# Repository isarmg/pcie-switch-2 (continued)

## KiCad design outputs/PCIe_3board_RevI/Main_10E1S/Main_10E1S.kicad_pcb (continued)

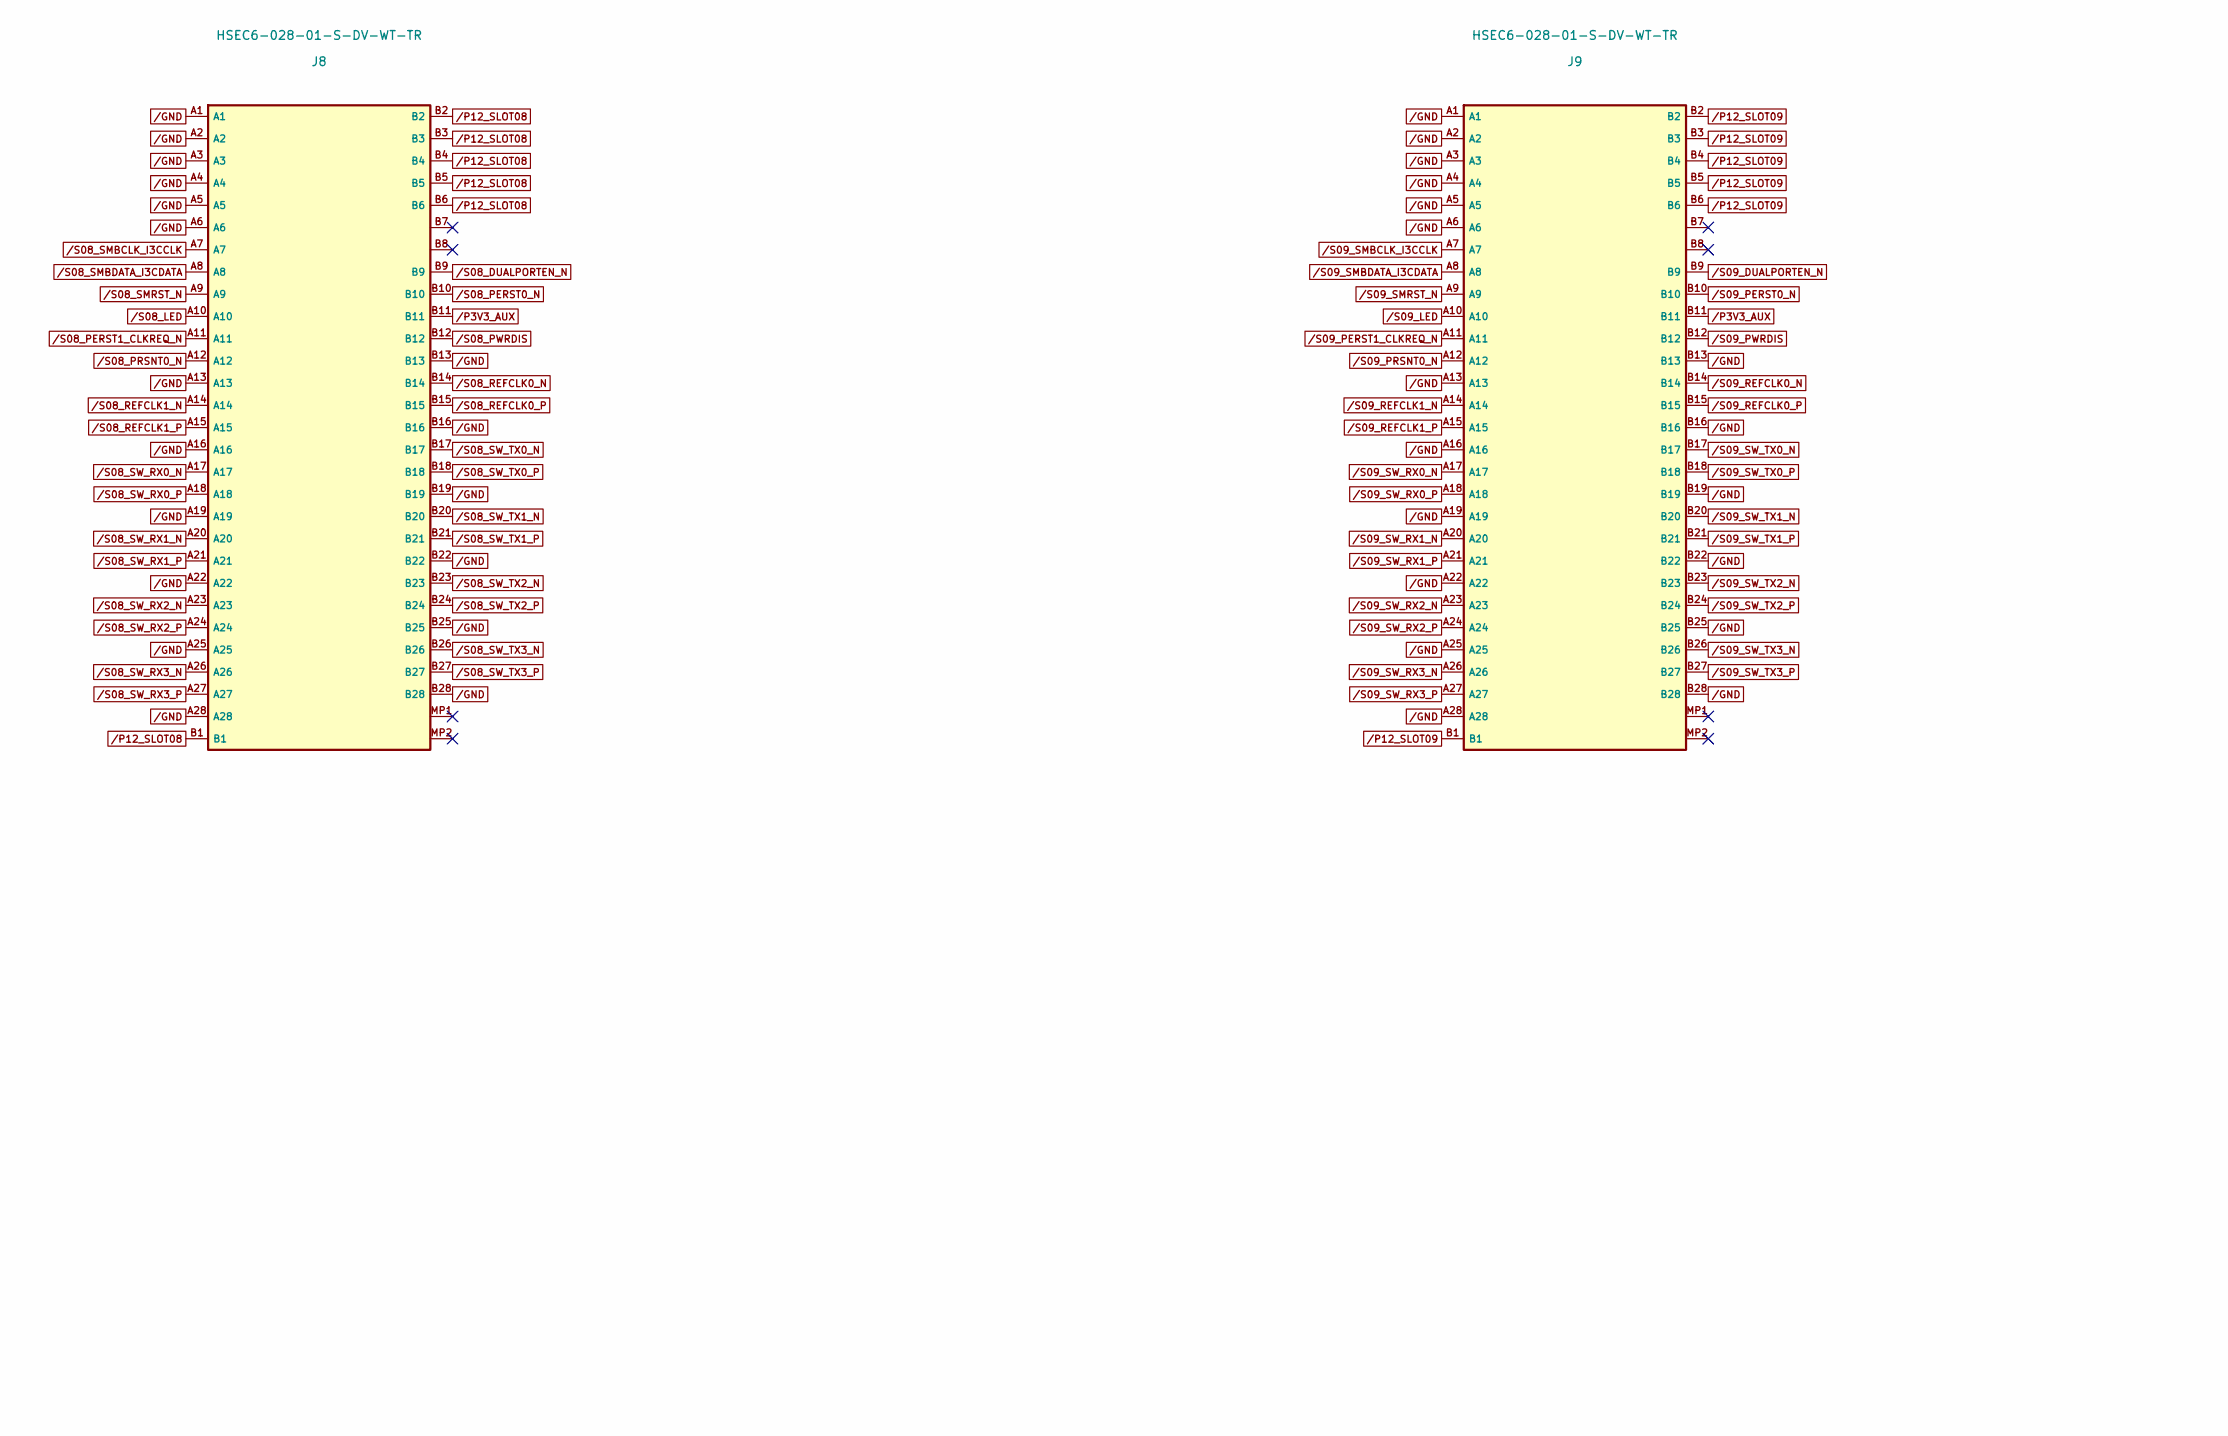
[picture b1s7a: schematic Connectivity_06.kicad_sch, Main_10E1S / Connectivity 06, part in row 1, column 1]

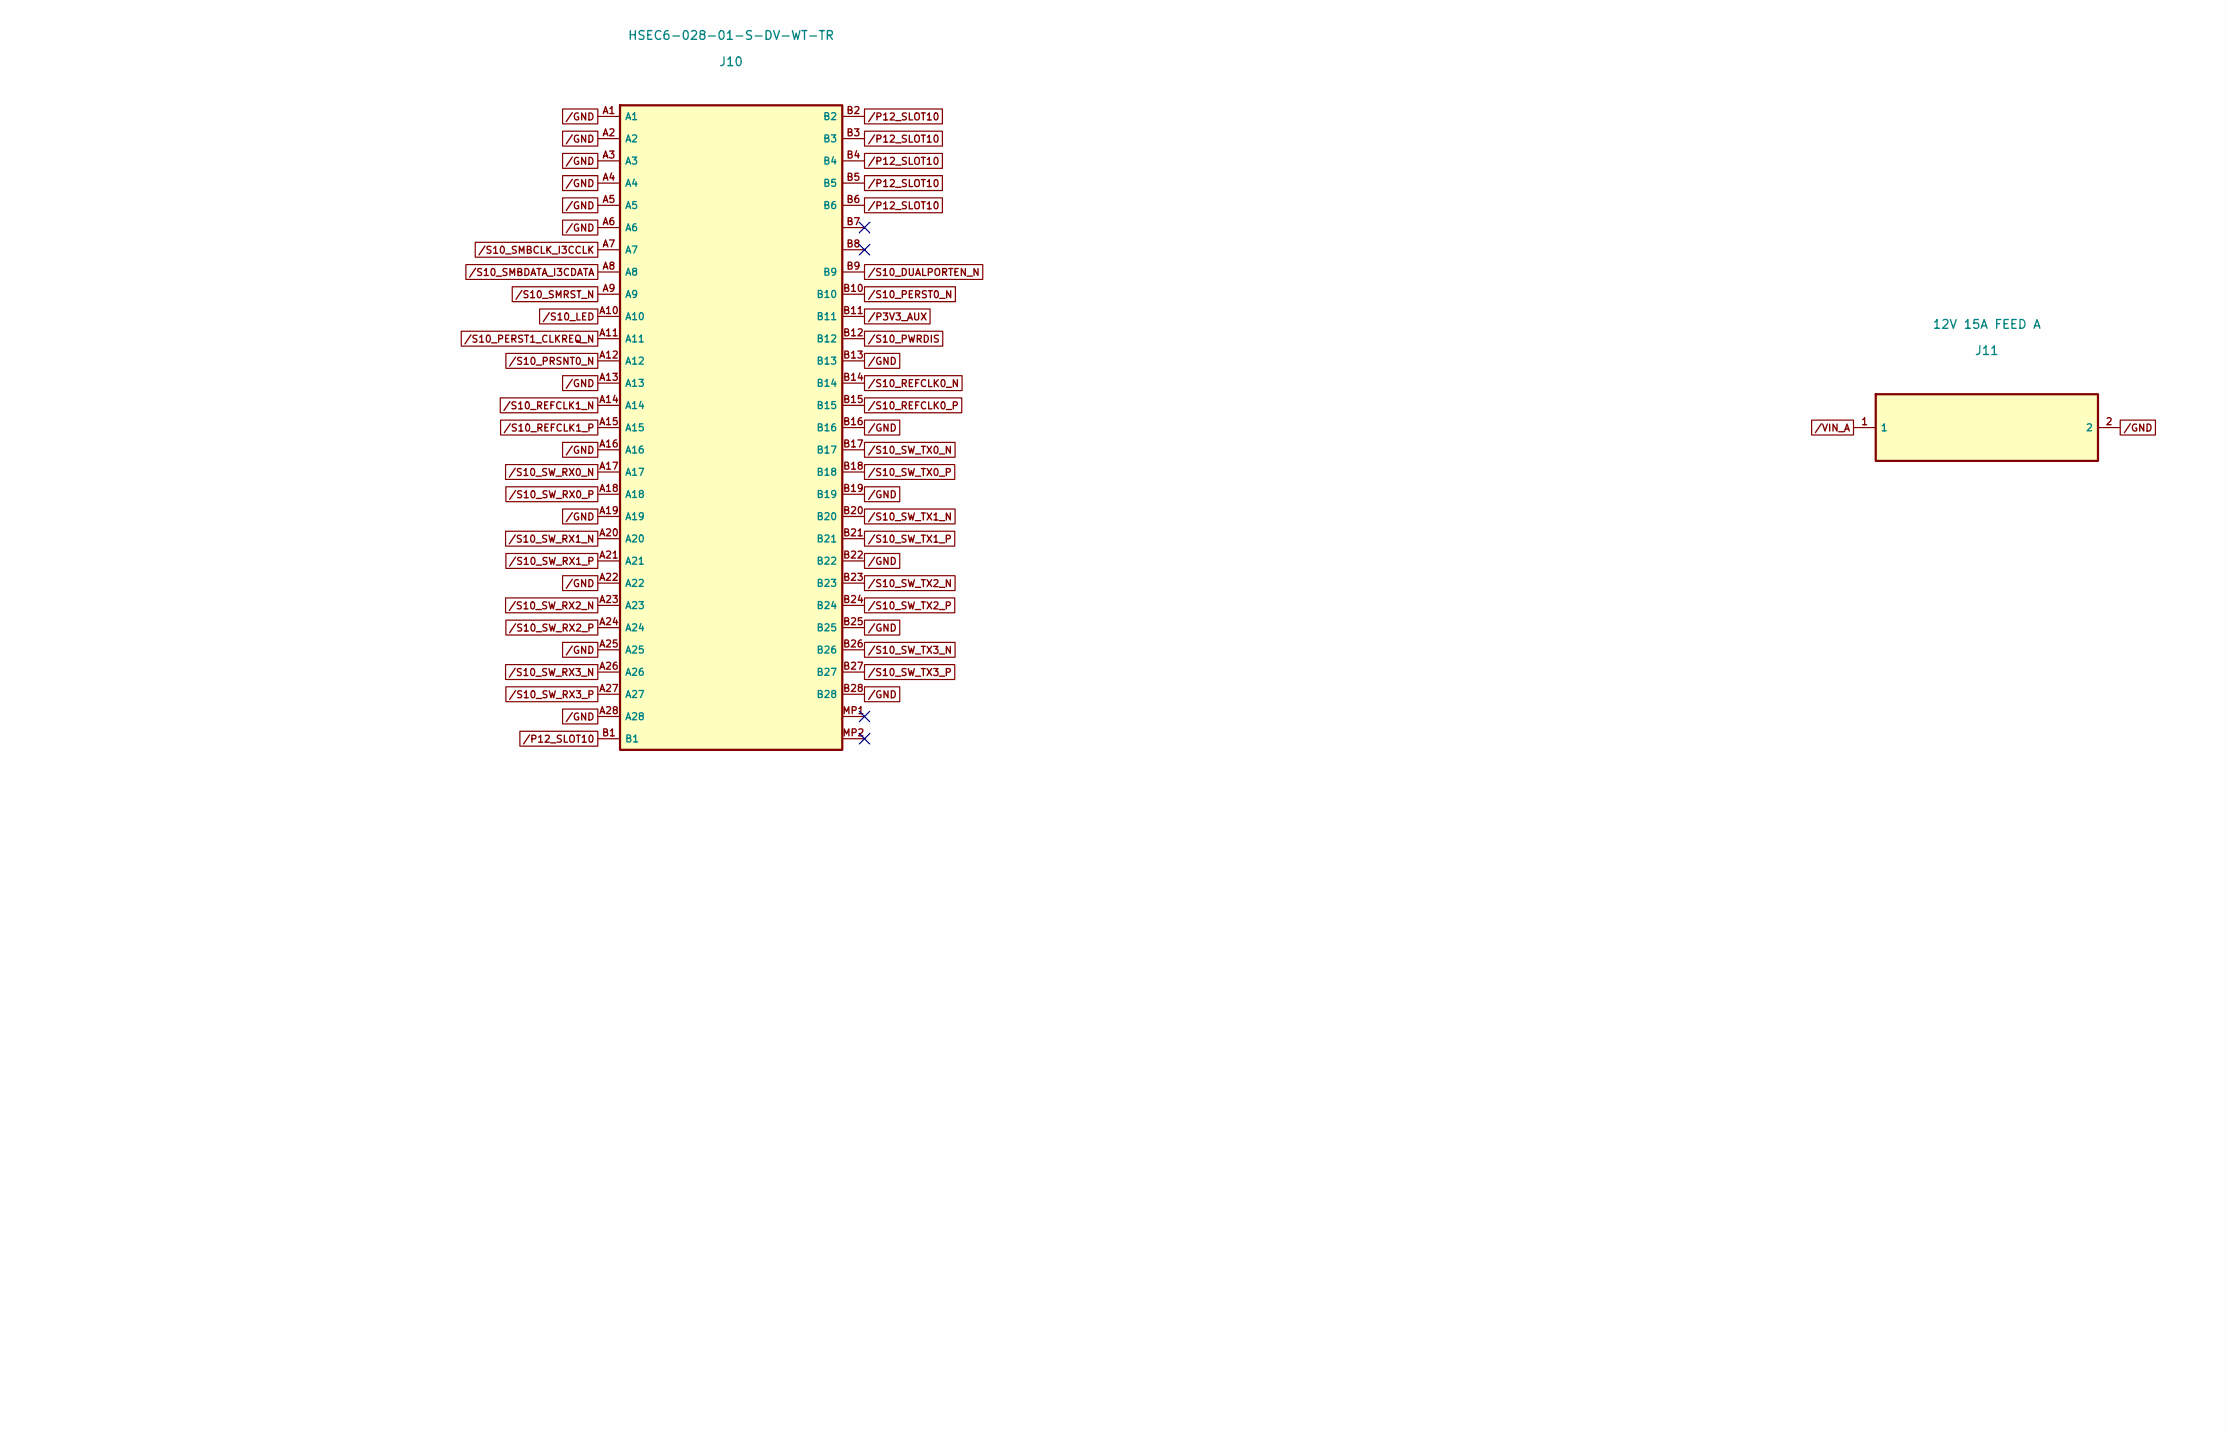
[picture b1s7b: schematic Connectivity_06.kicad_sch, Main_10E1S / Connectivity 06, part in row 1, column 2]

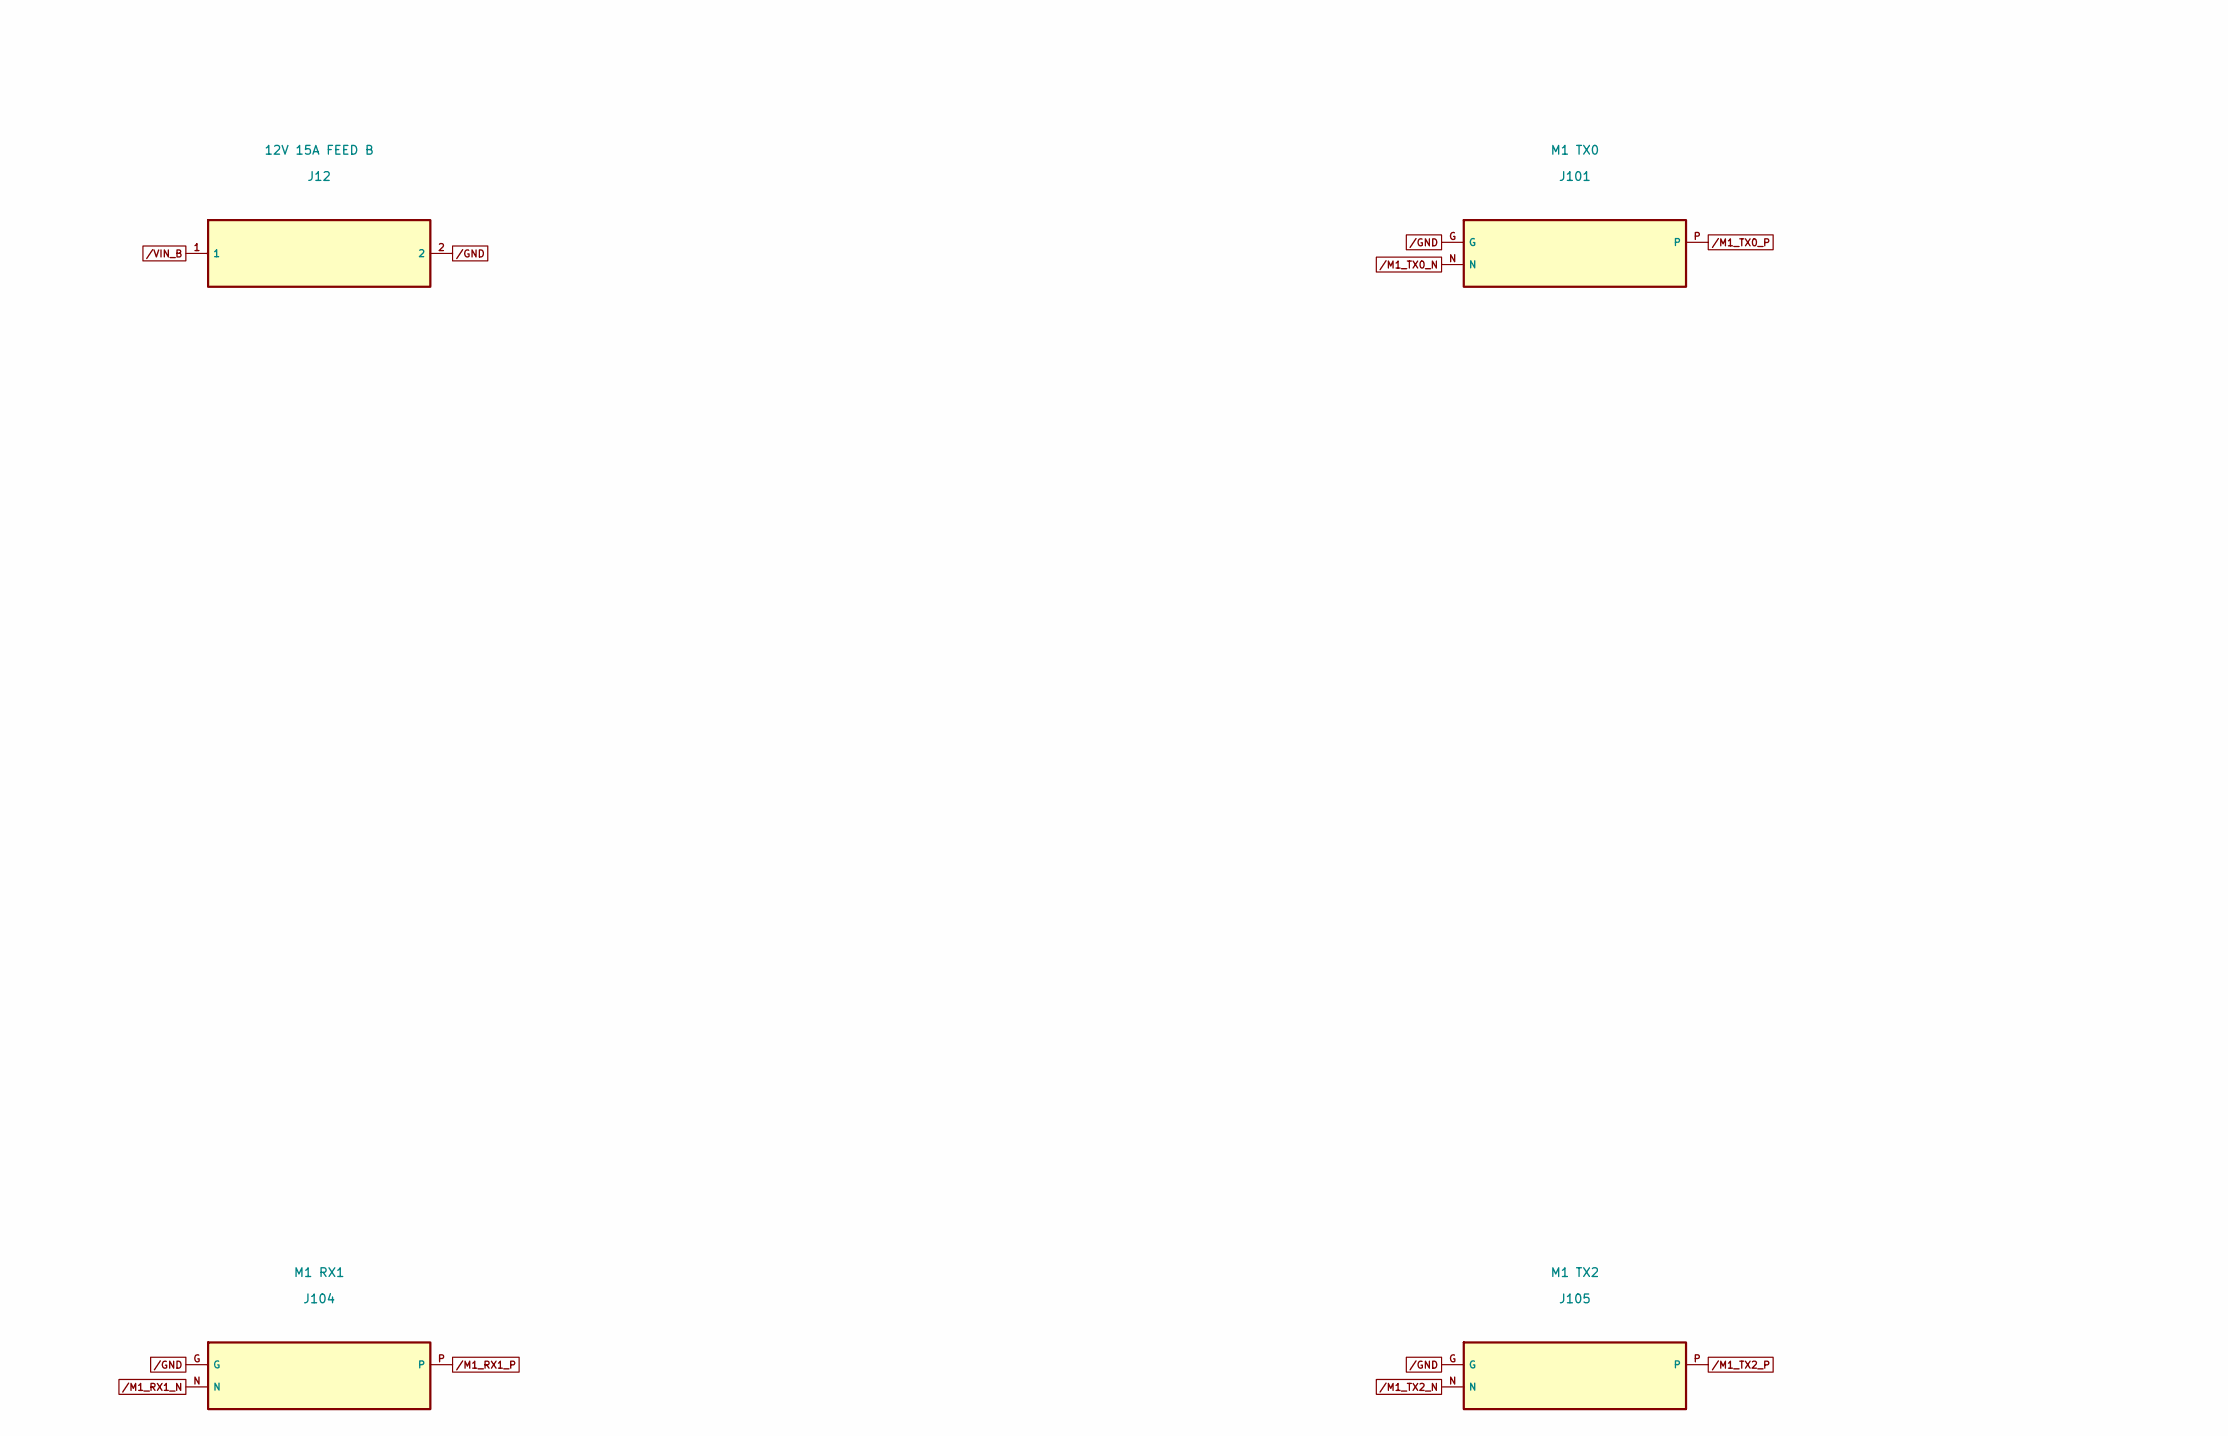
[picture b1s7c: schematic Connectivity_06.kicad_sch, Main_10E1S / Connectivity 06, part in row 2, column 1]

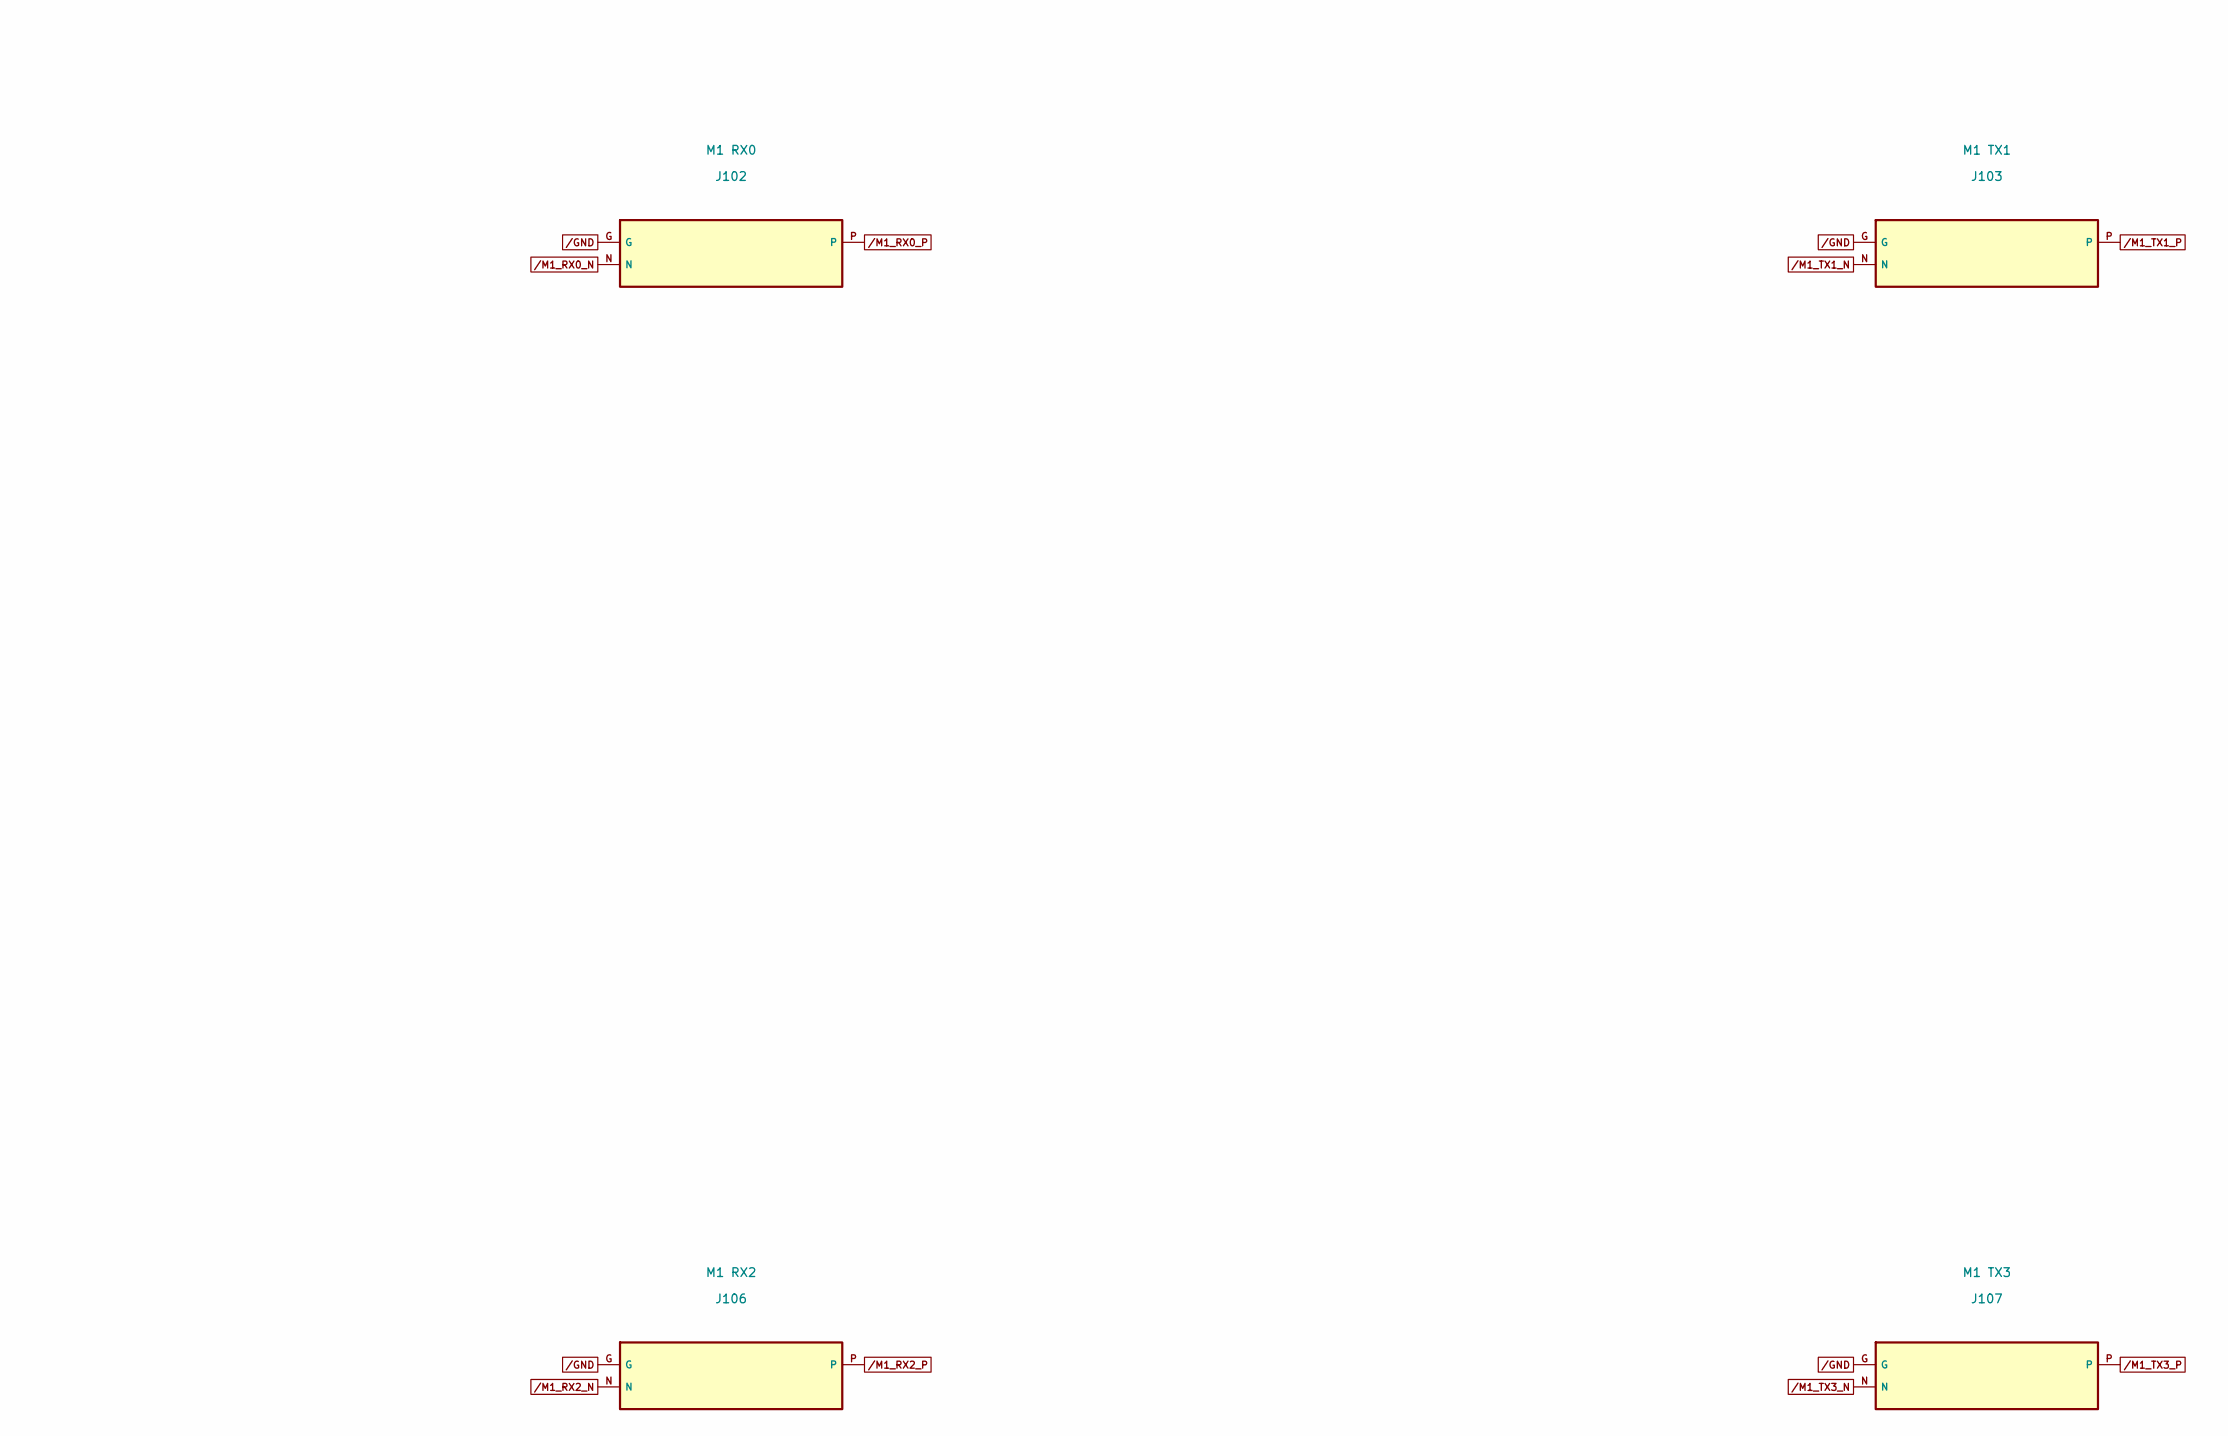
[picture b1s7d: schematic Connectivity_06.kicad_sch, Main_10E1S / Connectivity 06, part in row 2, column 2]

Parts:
J8, J9, J10: HSEC6-028-01-S-DV-WT-TR; Samtec_HSEC6-028-01-S-DV-WT
J11: 12V 15A FEED A; WireSolder_2x_8x5_P12
J12: 12V 15A FEED B; WireSolder_2x_8x5_P12
J101: M1 TX0; Twinax_85R_Solder_DRAFT
J102: M1 RX0; Twinax_85R_Solder_DRAFT
J103: M1 TX1; Twinax_85R_Solder_DRAFT
J104: M1 RX1; Twinax_85R_Solder_DRAFT
J105: M1 TX2; Twinax_85R_Solder_DRAFT
J106: M1 RX2; Twinax_85R_Solder_DRAFT
J107: M1 TX3; Twinax_85R_Solder_DRAFT

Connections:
/GND: J8.A1, J8.A2, J8.A3, J8.A4, J8.A5, J8.A6, J8.A13, J8.A16, J8.A19, J8.A22, J8.A25, J8.A28, J8.B13, J8.B16, J8.B19, J8.B22, J8.B25, J8.B28, J9.A1, J9.A2, J9.A3, J9.A4, J9.A5, J9.A6, J9.A13, J9.A16, J9.A19, J9.A22, J9.A25, J9.A28, J9.B13, J9.B16, J9.B19, J9.B22, J9.B25, J9.B28, J10.A1, J10.A2, J10.A3, J10.A4, J10.A5, J10.A6, J10.A13, J10.A16, J10.A19, J10.A22, J10.A25, J10.A28, J10.B13, J10.B16, J10.B19, J10.B22, J10.B25, J10.B28, J11.2, J12.2, J101.G, J102.G, J103.G, J104.G, J105.G, J106.G, J107.G; also elsewhere on the board
/M1_RX0_N: J102.N; also elsewhere on the board
/M1_RX0_P: J102.P; also elsewhere on the board
/M1_RX1_N: J104.N; also elsewhere on the board
/M1_RX1_P: J104.P; also elsewhere on the board
/M1_RX2_N: J106.N; also elsewhere on the board
/M1_RX2_P: J106.P; also elsewhere on the board
/M1_TX0_N: J101.N; also elsewhere on the board
/M1_TX0_P: J101.P; also elsewhere on the board
/M1_TX1_N: J103.N; also elsewhere on the board
/M1_TX1_P: J103.P; also elsewhere on the board
/M1_TX2_N: J105.N; also elsewhere on the board
/M1_TX2_P: J105.P; also elsewhere on the board
/M1_TX3_N: J107.N; also elsewhere on the board
/M1_TX3_P: J107.P; also elsewhere on the board
/P3V3_AUX: J8.B11, J9.B11, J10.B11; also elsewhere on the board
/P12_SLOT08: J8.B1, J8.B2, J8.B3, J8.B4, J8.B5, J8.B6; also elsewhere on the board
/P12_SLOT09: J9.B1, J9.B2, J9.B3, J9.B4, J9.B5, J9.B6; also elsewhere on the board
/P12_SLOT10: J10.B1, J10.B2, J10.B3, J10.B4, J10.B5, J10.B6; also elsewhere on the board
/S08_DUALPORTEN_N: J8.B9
/S08_LED: J8.A10
/S08_PERST0_N: J8.B10; also elsewhere on the board
/S08_PERST1_CLKREQ_N: J8.A11
/S08_PRSNT0_N: J8.A12
/S08_PWRDIS: J8.B12
/S08_REFCLK0_N: J8.B14; also elsewhere on the board
/S08_REFCLK0_P: J8.B15; also elsewhere on the board
/S08_REFCLK1_N: J8.A14; also elsewhere on the board
/S08_REFCLK1_P: J8.A15; also elsewhere on the board
/S08_SMBCLK_I3CCLK: J8.A7
/S08_SMBDATA_I3CDATA: J8.A8
/S08_SMRST_N: J8.A9
/S08_SW_RX0_N: J8.A17; also elsewhere on the board
/S08_SW_RX0_P: J8.A18; also elsewhere on the board
/S08_SW_RX1_N: J8.A20; also elsewhere on the board
/S08_SW_RX1_P: J8.A21; also elsewhere on the board
/S08_SW_RX2_N: J8.A23; also elsewhere on the board
/S08_SW_RX2_P: J8.A24; also elsewhere on the board
/S08_SW_RX3_N: J8.A26; also elsewhere on the board
/S08_SW_RX3_P: J8.A27; also elsewhere on the board
/S08_SW_TX0_N: J8.B17; also elsewhere on the board
/S08_SW_TX0_P: J8.B18; also elsewhere on the board
/S08_SW_TX1_N: J8.B20; also elsewhere on the board
/S08_SW_TX1_P: J8.B21; also elsewhere on the board
/S08_SW_TX2_N: J8.B23; also elsewhere on the board
/S08_SW_TX2_P: J8.B24; also elsewhere on the board
/S08_SW_TX3_N: J8.B26; also elsewhere on the board
/S08_SW_TX3_P: J8.B27; also elsewhere on the board
/S09_DUALPORTEN_N: J9.B9
/S09_LED: J9.A10
/S09_PERST0_N: J9.B10; also elsewhere on the board
/S09_PERST1_CLKREQ_N: J9.A11
/S09_PRSNT0_N: J9.A12
/S09_PWRDIS: J9.B12
/S09_REFCLK0_N: J9.B14; also elsewhere on the board
/S09_REFCLK0_P: J9.B15; also elsewhere on the board
/S09_REFCLK1_N: J9.A14; also elsewhere on the board
/S09_REFCLK1_P: J9.A15; also elsewhere on the board
/S09_SMBCLK_I3CCLK: J9.A7
/S09_SMBDATA_I3CDATA: J9.A8
/S09_SMRST_N: J9.A9
/S09_SW_RX0_N: J9.A17; also elsewhere on the board
/S09_SW_RX0_P: J9.A18; also elsewhere on the board
/S09_SW_RX1_N: J9.A20; also elsewhere on the board
/S09_SW_RX1_P: J9.A21; also elsewhere on the board
/S09_SW_RX2_N: J9.A23; also elsewhere on the board
/S09_SW_RX2_P: J9.A24; also elsewhere on the board
/S09_SW_RX3_N: J9.A26; also elsewhere on the board
/S09_SW_RX3_P: J9.A27; also elsewhere on the board
/S09_SW_TX0_N: J9.B17; also elsewhere on the board
/S09_SW_TX0_P: J9.B18; also elsewhere on the board
/S09_SW_TX1_N: J9.B20; also elsewhere on the board
/S09_SW_TX1_P: J9.B21; also elsewhere on the board
/S09_SW_TX2_N: J9.B23; also elsewhere on the board
/S09_SW_TX2_P: J9.B24; also elsewhere on the board
/S09_SW_TX3_N: J9.B26; also elsewhere on the board
/S09_SW_TX3_P: J9.B27; also elsewhere on the board
/S10_DUALPORTEN_N: J10.B9
/S10_LED: J10.A10
/S10_PERST0_N: J10.B10; also elsewhere on the board
/S10_PERST1_CLKREQ_N: J10.A11
/S10_PRSNT0_N: J10.A12
/S10_PWRDIS: J10.B12
/S10_REFCLK0_N: J10.B14; also elsewhere on the board
/S10_REFCLK0_P: J10.B15; also elsewhere on the board
/S10_REFCLK1_N: J10.A14; also elsewhere on the board
/S10_REFCLK1_P: J10.A15; also elsewhere on the board
/S10_SMBCLK_I3CCLK: J10.A7
/S10_SMBDATA_I3CDATA: J10.A8
/S10_SMRST_N: J10.A9
/S10_SW_RX0_N: J10.A17; also elsewhere on the board
/S10_SW_RX0_P: J10.A18; also elsewhere on the board
/S10_SW_RX1_N: J10.A20; also elsewhere on the board
/S10_SW_RX1_P: J10.A21; also elsewhere on the board
/S10_SW_RX2_N: J10.A23; also elsewhere on the board
/S10_SW_RX2_P: J10.A24; also elsewhere on the board
/S10_SW_RX3_N: J10.A26; also elsewhere on the board
/S10_SW_RX3_P: J10.A27; also elsewhere on the board
/S10_SW_TX0_N: J10.B17; also elsewhere on the board
/S10_SW_TX0_P: J10.B18; also elsewhere on the board
/S10_SW_TX1_N: J10.B20; also elsewhere on the board
/S10_SW_TX1_P: J10.B21; also elsewhere on the board
/S10_SW_TX2_N: J10.B23; also elsewhere on the board
/S10_SW_TX2_P: J10.B24; also elsewhere on the board
/S10_SW_TX3_N: J10.B26; also elsewhere on the board
/S10_SW_TX3_P: J10.B27; also elsewhere on the board
/VIN_A: J11.1; also elsewhere on the board
/VIN_B: J12.1; also elsewhere on the board
